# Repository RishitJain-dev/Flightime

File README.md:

# Flightime - Quadcopter

Flightime is a custom designed drone with a PLA Aero frame, 4 8520 brushed motors, and a PCB flight controller with a OV2640 camera mounted on the XIAO ESP32 S3 SENSE

> Weighs: 132.6g

I designed this as an example project for [Lift Off](liftoff-ysws.vercel.app), where you design a drone, and get the components to build it and if its a great project, then even a drone controller!

### Features
- OV2640 FPV Camera
- Bluetooth and WiFi capabilities
- < 150g
- Power Switch
- 8520 Brushed motors
- $200 total price (including tools!)

## PCB

The PCB was made in KiCAD! It has:
- GY-521 gyroscope
- XIAO ESP32 S3 sense
- Various resistors
- Various SMD & TH capacitors
- SMD MOFSETs

## CAD

The CAD was designed exclusively in Onshape. The 2 parts fit together with 4 M3 screws and nuts, it doesn't require any heatset inserts, you screw directly into the PLA.

There are cut-outs in each piece so that wires can fit through. This is a pusher drone, the motors are press fit and the propellers face towards the ground.

## Assembly  

Use the schematic diagram on Kicanvas to solder one side of the wires to the board before assembly. Then place the board, mount it using the screws and nuts and take the wires to the motors and solder the other side there. 

## Firmware

We move by slowing down certain motors and speeding up others, this causes it to lean and tilt towards the direction its meant to be going, and begins to accelerate. 
In the final firmware, it will be controlled through bluetooth on a computer or phone.

# Renders

Here are some renders I made in Onshape!

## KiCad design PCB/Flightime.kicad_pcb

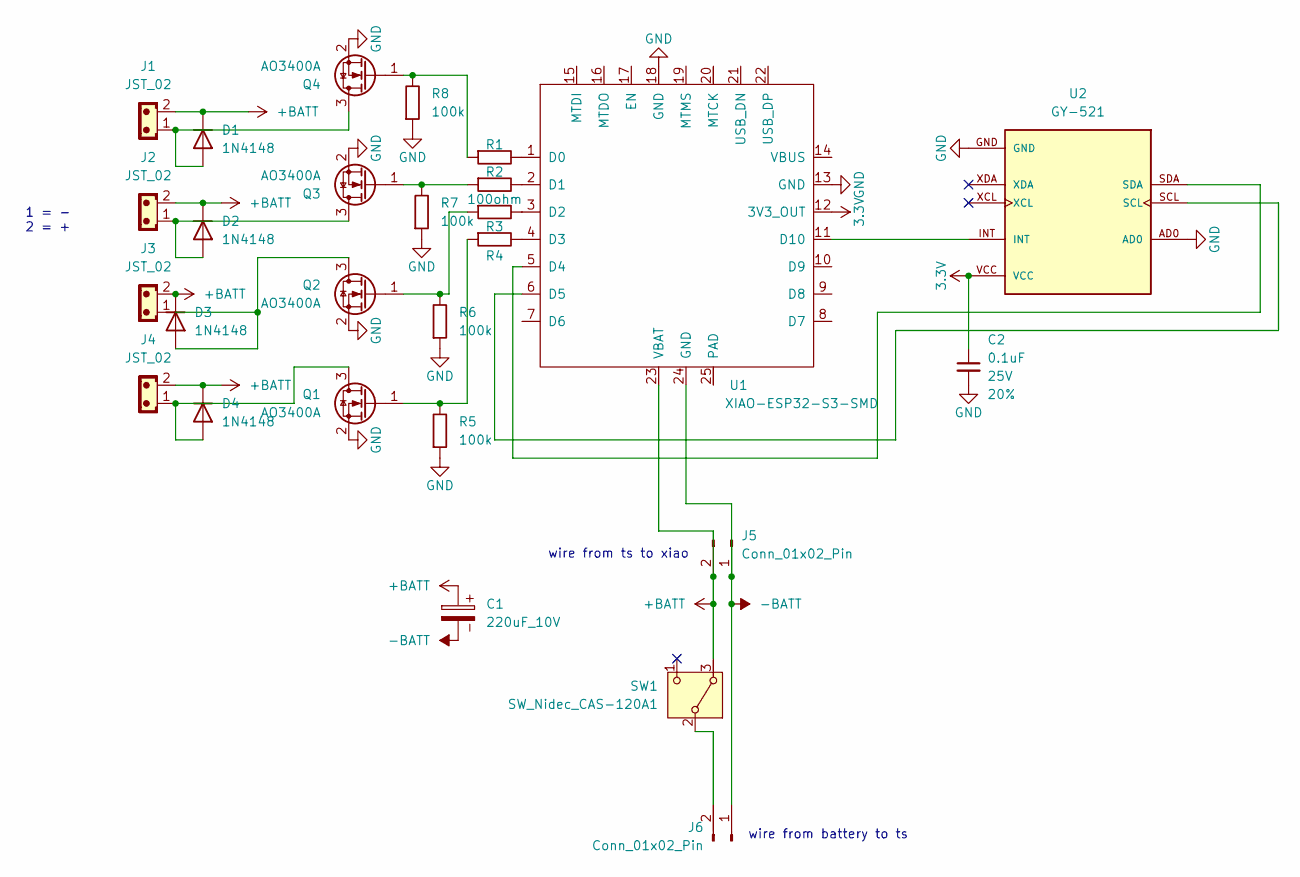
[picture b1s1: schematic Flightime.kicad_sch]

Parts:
C1: 220uF_10V; CP_Radial_D6.3mm_P2.50mm
C2: 0.1uF; C_0603_1608Metric; Voltage 25V; Tolerance 20%
D1, D2, D3, D4: 1N4148; D_DO-35_SOD27_P7.62mm_Horizontal
J1, J2, J3, J4: JST_02; JST_EH_B2B-EH-A_1x02_P2.50mm_Vertical
J5, J6: Conn_01x02_Pin; JST_EH_B2B-EH-A_1x02_P2.50mm_Vertical
Q1, Q2, Q3, Q4: AO3400A; SOT-23
R1, R2, R3, R4: 100ohm; R_Axial_DIN0207_L6.3mm_D2.5mm_P10.16mm_Horizontal
R5, R6, R7, R8: 100k; R_Axial_DIN0207_L6.3mm_D2.5mm_P10.16mm_Horizontal
SW1: SW_Nidec_CAS-120A1; Nidec_Copal_CAS-120A
U1: XIAO-ESP32-S3-SMD
U2: GY-521; MODULE_GY-521; PARTREV NA

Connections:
3.3V: C2.1, U1.12 (3V3_OUT), U2.VCC
-BATT: C1.2, J5.1, J6.1, U1.24 (GND)
GND: C2.2, Q1.2 (S), Q2.2 (S), Q3.2 (S), Q4.2 (S), R5.1, R6.1, R7.1, R8.1, U1.13 (GND), U1.18 (GND), U2.AD0, U2.GND
unnamed: D1.2 (A), J1.1, Q4.3 (D)
unnamed: D2.2 (A), J2.1, Q3.3 (D)
unnamed: D3.2 (A), J3.1, Q2.3 (D)
unnamed: D4.2 (A), J4.1, Q1.3 (D)
unnamed: Q1.1 (G), R4.1, R5.2
unnamed: Q2.1 (G), R3.1, R6.2
unnamed: Q3.1 (G), R2.1, R7.2
unnamed: Q4.1 (G), R1.1, R8.2
unnamed: R1.2, U1.1 (D0)
unnamed: R2.2, U1.2 (D1)
unnamed: R3.2, U1.3 (D2)
unnamed: R4.2, U1.4 (D3)
unnamed: U1.5 (D4), U2.SDA
unnamed: U1.6 (D5), U2.SCL
unnamed: U1.11 (D10), U2.INT

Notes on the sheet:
wire from ts to xiao
wire from battery to ts
1 = - 2 = +

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
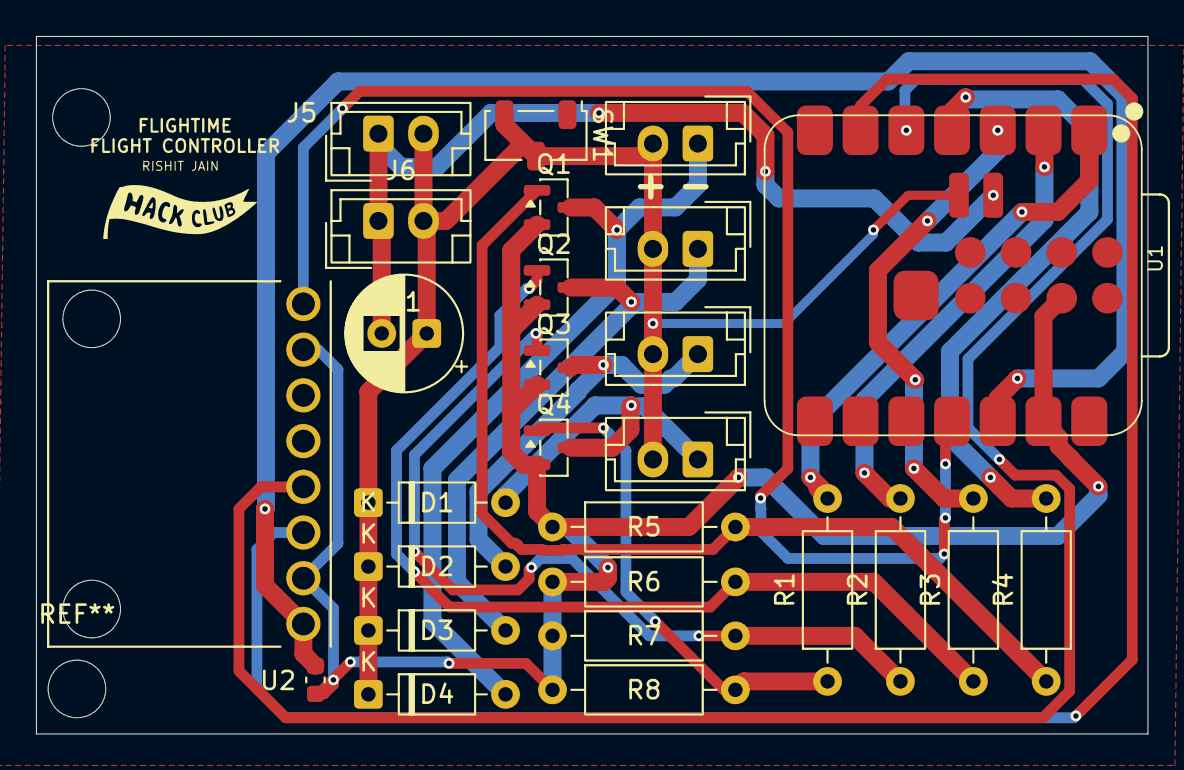
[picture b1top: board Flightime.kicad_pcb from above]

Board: 2 copper layers, 61.8 x 38.8 mm, 27 parts (0 on the bottom side), 19 nets.

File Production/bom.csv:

Designator,Footprint,Quantity,Value,LCSC Part #
,,1,,
C1,CP_Radial_D6.3mm_P2.50mm,1,220uF_10V,
C2,0603,1,0.1uF,
"D1, D2, D3, D4",D_DO-35_SOD27_P7.62mm_Horizontal,4,1N4148,
"J1, J2, J3, J4",JST_EH_B2B-EH-A_1x02_P2.50mm_Vertical,4,JST_02,
"J5, J6",JST_EH_B2B-EH-A_1x02_P2.50mm_Vertical,2,Conn_01x02_Pin,
"Q1, Q2, Q3, Q4",SOT-23,4,AO3400A,
"R1, R2, R3, R4",R_Axial_DIN0207_L6.3mm_D2.5mm_P10.16mm_Horizontal,4,100ohm,
"R5, R6, R7, R8",R_Axial_DIN0207_L6.3mm_D2.5mm_P10.16mm_Horizontal,4,100k,
SW1,Nidec_Copal_CAS-120A,1,SW_Nidec_CAS-120A1,
U1,XIAO-ESP32-S3-SMD,1,XIAO-ESP32-S3-SMD,
U2,MODULE_GY-521,1,GY-521,
